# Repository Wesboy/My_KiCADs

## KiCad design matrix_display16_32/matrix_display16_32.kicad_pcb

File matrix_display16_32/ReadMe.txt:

更新
1 更换esp8266为esp32
3 更换TYPE-C座子
4 更换充电电池方案
5 电池电量检测
	电量低于20
6 充电提示ADC检测
7 天气
8 协议通信
   时间
   天气
   电量
   交互
   
下一版
 
9 增加两个贴片麦硅 AP3722AT

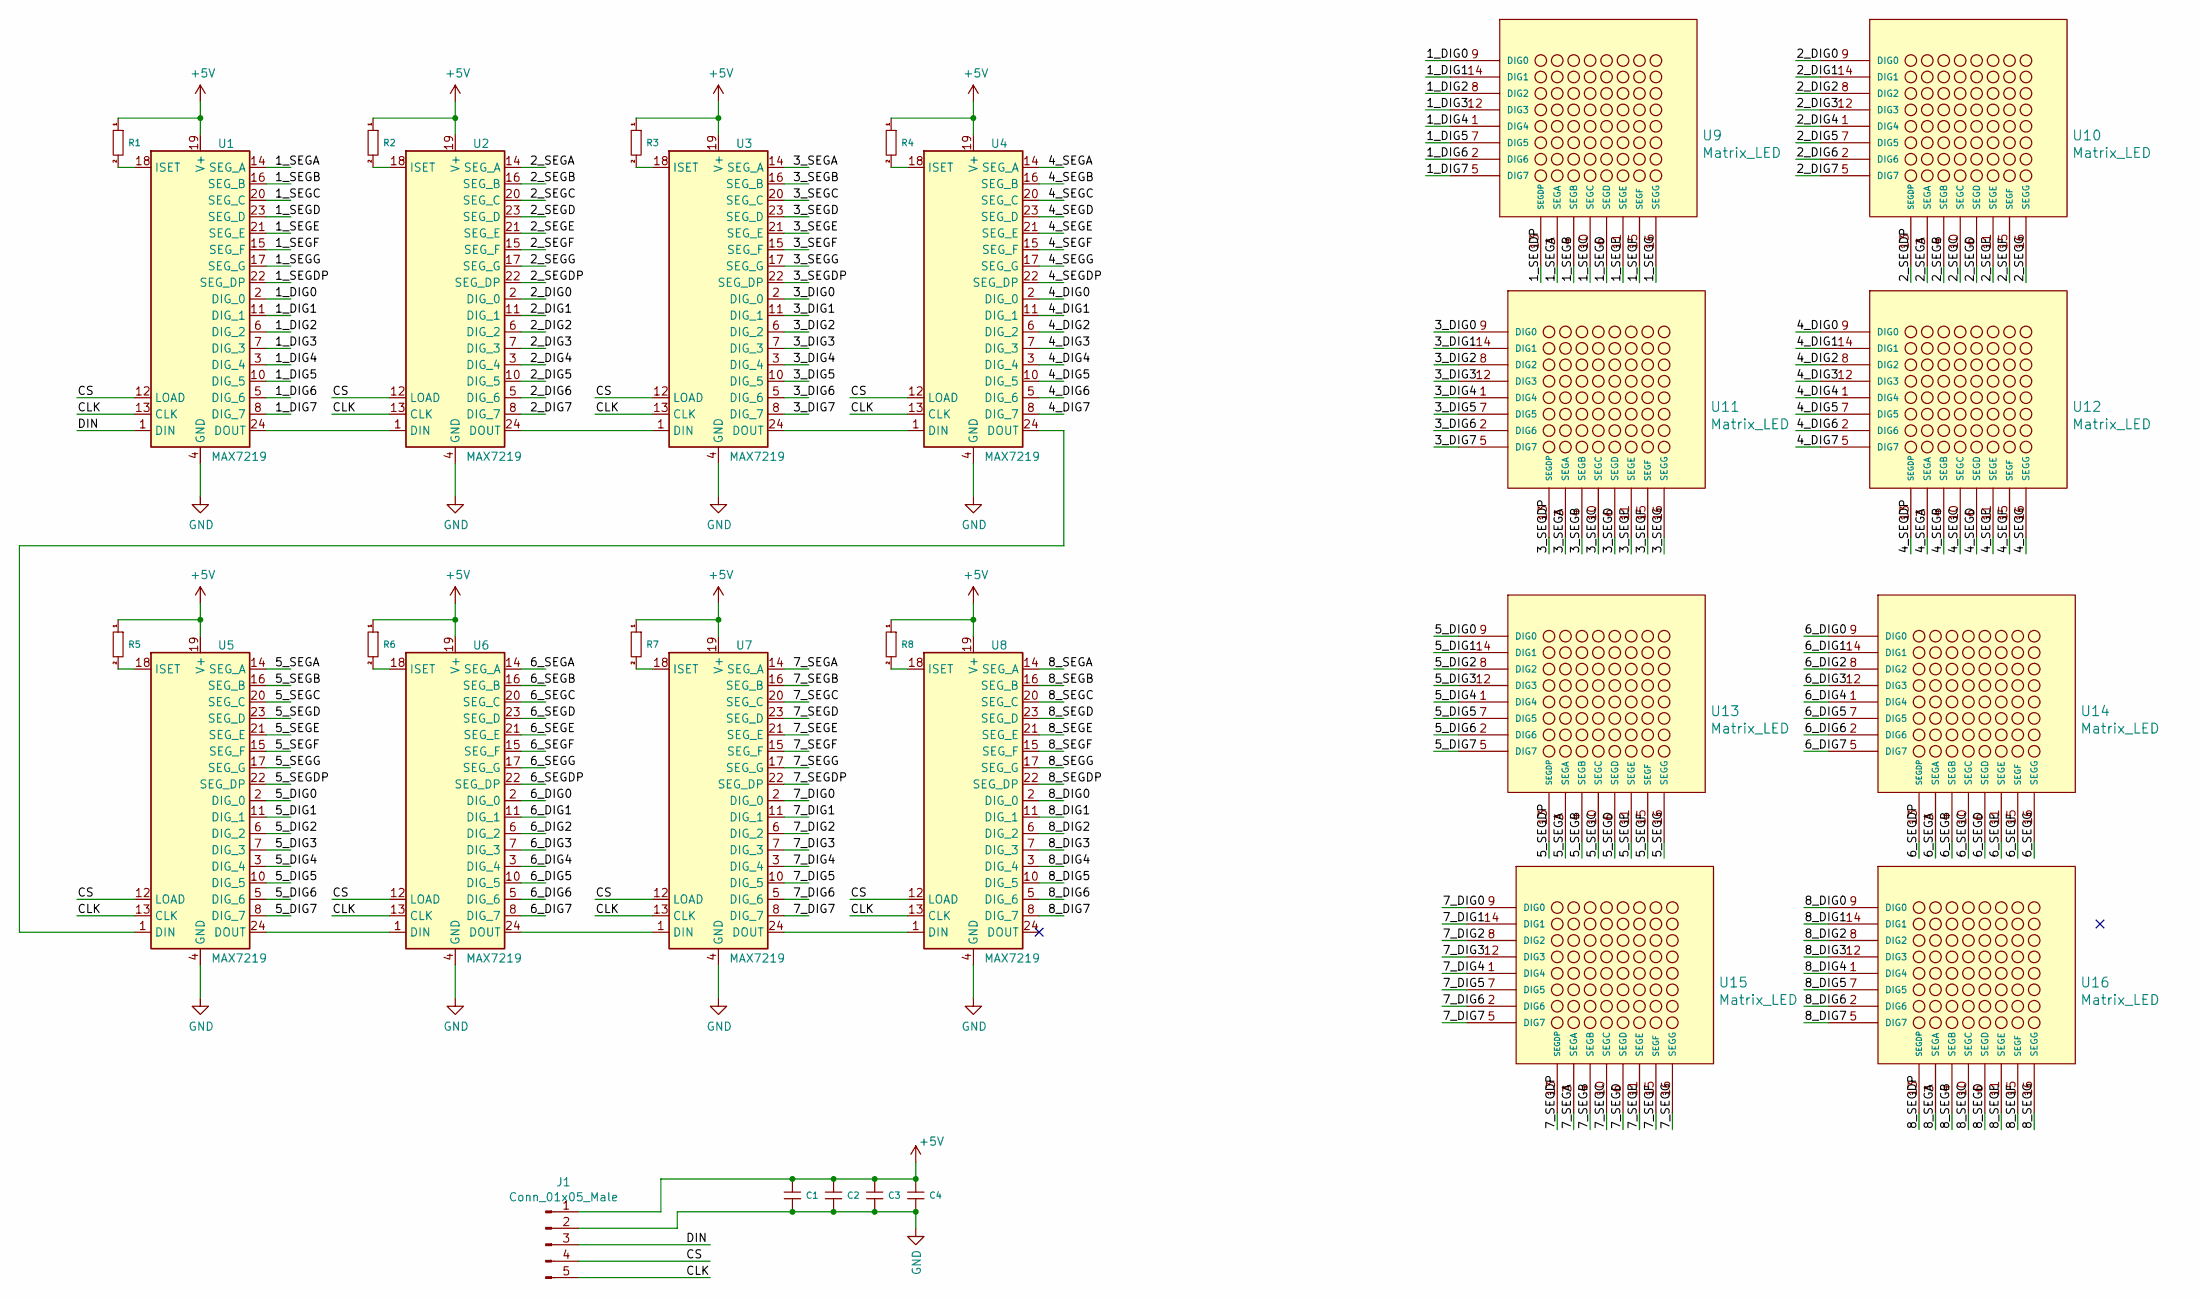
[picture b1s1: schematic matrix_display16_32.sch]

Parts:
C1, C2, C3, C4: C(MM)-LibCool; 0603_C
J1: Conn_01x05_Male; PinHeader_1x05_P2.54mm_Vertical
R1, R2, R3, R4, R5, R6, R7, R8: RES(M)-LibCool; 0603_R
U1, U2, U3, U4, U5, U6, U7, U8: MAX7219; SOIC-24W_7.5x15.4mm_P1.27mm
U9, U10, U11, U12, U13, U14, U15, U16: Matrix_LED

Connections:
+5V: C1.1, C2.1, C3.1, C4.1, J1.1, R1.1, R2.1, R3.1, R4.1, R5.1, R6.1, R7.1, R8.1, U1.19 (V+), U2.19 (V+), U3.19 (V+), U4.19 (V+), U5.19 (V+), U6.19 (V+), U7.19 (V+), U8.19 (V+)
/1_DIG0: U1.2 (DIG_0), U9.9 (DIG0)
/1_DIG1: U1.11 (DIG_1), U9.14 (DIG1)
/1_DIG2: U1.6 (DIG_2), U9.8 (DIG2)
/1_DIG3: U1.7 (DIG_3), U9.12 (DIG3)
/1_DIG4: U1.3 (DIG_4), U9.1 (DIG4)
/1_DIG5: U1.10 (DIG_5), U9.7 (DIG5)
/1_DIG6: U1.5 (DIG_6), U9.2 (DIG6)
/1_DIG7: U1.8 (DIG_7), U9.5 (DIG7)
/1_SEGA: U1.14 (SEG_A), U9.3 (SEGA)
/1_SEGB: U1.16 (SEG_B), U9.4 (SEGB)
/1_SEGC: U1.20 (SEG_C), U9.10 (SEGC)
/1_SEGD: U1.23 (SEG_D), U9.6 (SEGD)
/1_SEGDP: U1.22 (SEG_DP), U9.13 (SEGDP)
/1_SEGE: U1.21 (SEG_E), U9.11 (SEGE)
/1_SEGF: U1.15 (SEG_F), U9.15 (SEGF)
/1_SEGG: U1.17 (SEG_G), U9.16 (SEGG)
/2_DIG0: U2.2 (DIG_0), U10.9 (DIG0)
/2_DIG1: U2.11 (DIG_1), U10.14 (DIG1)
/2_DIG2: U2.6 (DIG_2), U10.8 (DIG2)
/2_DIG3: U2.7 (DIG_3), U10.12 (DIG3)
/2_DIG4: U2.3 (DIG_4), U10.1 (DIG4)
/2_DIG5: U2.10 (DIG_5), U10.7 (DIG5)
/2_DIG6: U2.5 (DIG_6), U10.2 (DIG6)
/2_DIG7: U2.8 (DIG_7), U10.5 (DIG7)
/2_SEGA: U2.14 (SEG_A), U10.3 (SEGA)
/2_SEGB: U2.16 (SEG_B), U10.4 (SEGB)
/2_SEGC: U2.20 (SEG_C), U10.10 (SEGC)
/2_SEGD: U2.23 (SEG_D), U10.6 (SEGD)
/2_SEGDP: U2.22 (SEG_DP), U10.13 (SEGDP)
/2_SEGE: U2.21 (SEG_E), U10.11 (SEGE)
/2_SEGF: U2.15 (SEG_F), U10.15 (SEGF)
/2_SEGG: U2.17 (SEG_G), U10.16 (SEGG)
/3_DIG0: U3.2 (DIG_0), U11.9 (DIG0)
/3_DIG1: U3.11 (DIG_1), U11.14 (DIG1)
/3_DIG2: U3.6 (DIG_2), U11.8 (DIG2)
/3_DIG3: U3.7 (DIG_3), U11.12 (DIG3)
/3_DIG4: U3.3 (DIG_4), U11.1 (DIG4)
/3_DIG5: U3.10 (DIG_5), U11.7 (DIG5)
/3_DIG6: U3.5 (DIG_6), U11.2 (DIG6)
/3_DIG7: U3.8 (DIG_7), U11.5 (DIG7)
/3_SEGA: U3.14 (SEG_A), U11.3 (SEGA)
/3_SEGB: U3.16 (SEG_B), U11.4 (SEGB)
/3_SEGC: U3.20 (SEG_C), U11.10 (SEGC)
/3_SEGD: U3.23 (SEG_D), U11.6 (SEGD)
/3_SEGDP: U3.22 (SEG_DP), U11.13 (SEGDP)
/3_SEGE: U3.21 (SEG_E), U11.11 (SEGE)
/3_SEGF: U3.15 (SEG_F), U11.15 (SEGF)
/3_SEGG: U3.17 (SEG_G), U11.16 (SEGG)
/4_DIG0: U4.2 (DIG_0), U12.9 (DIG0)
/4_DIG1: U4.11 (DIG_1), U12.14 (DIG1)
/4_DIG2: U4.6 (DIG_2), U12.8 (DIG2)
/4_DIG3: U4.7 (DIG_3), U12.12 (DIG3)
/4_DIG4: U4.3 (DIG_4), U12.1 (DIG4)
/4_DIG5: U4.10 (DIG_5), U12.7 (DIG5)
/4_DIG6: U4.5 (DIG_6), U12.2 (DIG6)
/4_DIG7: U4.8 (DIG_7), U12.5 (DIG7)
/4_SEGA: U4.14 (SEG_A), U12.3 (SEGA)
/4_SEGB: U4.16 (SEG_B), U12.4 (SEGB)
/4_SEGC: U4.20 (SEG_C), U12.10 (SEGC)
/4_SEGD: U4.23 (SEG_D), U12.6 (SEGD)
/4_SEGDP: U4.22 (SEG_DP), U12.13 (SEGDP)
/4_SEGE: U4.21 (SEG_E), U12.11 (SEGE)
/4_SEGF: U4.15 (SEG_F), U12.15 (SEGF)
/4_SEGG: U4.17 (SEG_G), U12.16 (SEGG)
/5_DIG0: U5.2 (DIG_0), U13.9 (DIG0)
/5_DIG1: U5.11 (DIG_1), U13.14 (DIG1)
/5_DIG2: U5.6 (DIG_2), U13.8 (DIG2)
/5_DIG3: U5.7 (DIG_3), U13.12 (DIG3)
/5_DIG4: U5.3 (DIG_4), U13.1 (DIG4)
/5_DIG5: U5.10 (DIG_5), U13.7 (DIG5)
/5_DIG6: U5.5 (DIG_6), U13.2 (DIG6)
/5_DIG7: U5.8 (DIG_7), U13.5 (DIG7)
/5_SEGA: U5.14 (SEG_A), U13.3 (SEGA)
/5_SEGB: U5.16 (SEG_B), U13.4 (SEGB)
/5_SEGC: U5.20 (SEG_C), U13.10 (SEGC)
/5_SEGD: U5.23 (SEG_D), U13.6 (SEGD)
/5_SEGDP: U5.22 (SEG_DP), U13.13 (SEGDP)
/5_SEGE: U5.21 (SEG_E), U13.11 (SEGE)
/5_SEGF: U5.15 (SEG_F), U13.15 (SEGF)
/5_SEGG: U5.17 (SEG_G), U13.16 (SEGG)
/6_DIG0: U6.2 (DIG_0), U14.9 (DIG0)
/6_DIG1: U6.11 (DIG_1), U14.14 (DIG1)
/6_DIG2: U6.6 (DIG_2), U14.8 (DIG2)
/6_DIG3: U6.7 (DIG_3), U14.12 (DIG3)
/6_DIG4: U6.3 (DIG_4), U14.1 (DIG4)
/6_DIG5: U6.10 (DIG_5), U14.7 (DIG5)
/6_DIG6: U6.5 (DIG_6), U14.2 (DIG6)
/6_DIG7: U6.8 (DIG_7), U14.5 (DIG7)
/6_SEGA: U6.14 (SEG_A), U14.3 (SEGA)
/6_SEGB: U6.16 (SEG_B), U14.4 (SEGB)
/6_SEGC: U6.20 (SEG_C), U14.10 (SEGC)
/6_SEGD: U6.23 (SEG_D), U14.6 (SEGD)
/6_SEGDP: U6.22 (SEG_DP), U14.13 (SEGDP)
/6_SEGE: U6.21 (SEG_E), U14.11 (SEGE)
/6_SEGF: U6.15 (SEG_F), U14.15 (SEGF)
/6_SEGG: U6.17 (SEG_G), U14.16 (SEGG)
/7_DIG0: U7.2 (DIG_0), U15.9 (DIG0)
/7_DIG1: U7.11 (DIG_1), U15.14 (DIG1)
/7_DIG2: U7.6 (DIG_2), U15.8 (DIG2)
/7_DIG3: U7.7 (DIG_3), U15.12 (DIG3)
/7_DIG4: U7.3 (DIG_4), U15.1 (DIG4)
/7_DIG5: U7.10 (DIG_5), U15.7 (DIG5)
/7_DIG6: U7.5 (DIG_6), U15.2 (DIG6)
/7_DIG7: U7.8 (DIG_7), U15.5 (DIG7)
/7_SEGA: U7.14 (SEG_A), U15.3 (SEGA)
/7_SEGB: U7.16 (SEG_B), U15.4 (SEGB)
/7_SEGC: U7.20 (SEG_C), U15.10 (SEGC)
/7_SEGD: U7.23 (SEG_D), U15.6 (SEGD)
/7_SEGDP: U7.22 (SEG_DP), U15.13 (SEGDP)
/7_SEGE: U7.21 (SEG_E), U15.11 (SEGE)
/7_SEGF: U7.15 (SEG_F), U15.15 (SEGF)
/7_SEGG: U7.17 (SEG_G), U15.16 (SEGG)
/8_DIG0: U8.2 (DIG_0), U16.9 (DIG0)
/8_DIG1: U8.11 (DIG_1), U16.14 (DIG1)
/8_DIG2: U8.6 (DIG_2), U16.8 (DIG2)
/8_DIG3: U8.7 (DIG_3), U16.12 (DIG3)
/8_DIG4: U8.3 (DIG_4), U16.1 (DIG4)
/8_DIG5: U8.10 (DIG_5), U16.7 (DIG5)
/8_DIG6: U8.5 (DIG_6), U16.2 (DIG6)
/8_DIG7: U8.8 (DIG_7), U16.5 (DIG7)
/8_SEGA: U8.14 (SEG_A), U16.3 (SEGA)
/8_SEGB: U8.16 (SEG_B), U16.4 (SEGB)
/8_SEGC: U8.20 (SEG_C), U16.10 (SEGC)
/8_SEGD: U8.23 (SEG_D), U16.6 (SEGD)
/8_SEGDP: U8.22 (SEG_DP), U16.13 (SEGDP)
/8_SEGE: U8.21 (SEG_E), U16.11 (SEGE)
/8_SEGF: U8.15 (SEG_F), U16.15 (SEGF)
/8_SEGG: U8.17 (SEG_G), U16.16 (SEGG)
/CLK: J1.5, U1.13 (CLK), U2.13 (CLK), U3.13 (CLK), U4.13 (CLK), U5.13 (CLK), U6.13 (CLK), U7.13 (CLK), U8.13 (CLK)
/CS: J1.4, U1.12 (LOAD), U2.12 (LOAD), U3.12 (LOAD), U4.12 (LOAD), U5.12 (LOAD), U6.12 (LOAD), U7.12 (LOAD), U8.12 (LOAD)
/DIN: J1.3, U1.1 (DIN)
GND: C1.2, C2.2, C3.2, C4.2, J1.2, U1.4 (GND), U1.9 (GND), U2.4 (GND), U2.9 (GND), U3.4 (GND), U3.9 (GND), U4.4 (GND), U4.9 (GND), U5.4 (GND), U5.9 (GND), U6.4 (GND), U6.9 (GND), U7.4 (GND), U7.9 (GND), U8.4 (GND), U8.9 (GND)
unnamed: R1.2, U1.18 (ISET)
unnamed: R2.2, U2.18 (ISET)
unnamed: R3.2, U3.18 (ISET)
unnamed: R4.2, U4.18 (ISET)
unnamed: R5.2, U5.18 (ISET)
unnamed: R6.2, U6.18 (ISET)
unnamed: R7.2, U7.18 (ISET)
unnamed: R8.2, U8.18 (ISET)
unnamed: U1.24 (DOUT), U2.1 (DIN)
unnamed: U2.24 (DOUT), U3.1 (DIN)
unnamed: U3.24 (DOUT), U4.1 (DIN)
unnamed: U4.24 (DOUT), U5.1 (DIN)
unnamed: U5.24 (DOUT), U6.1 (DIN)
unnamed: U6.24 (DOUT), U7.1 (DIN)
unnamed: U7.24 (DOUT), U8.1 (DIN)

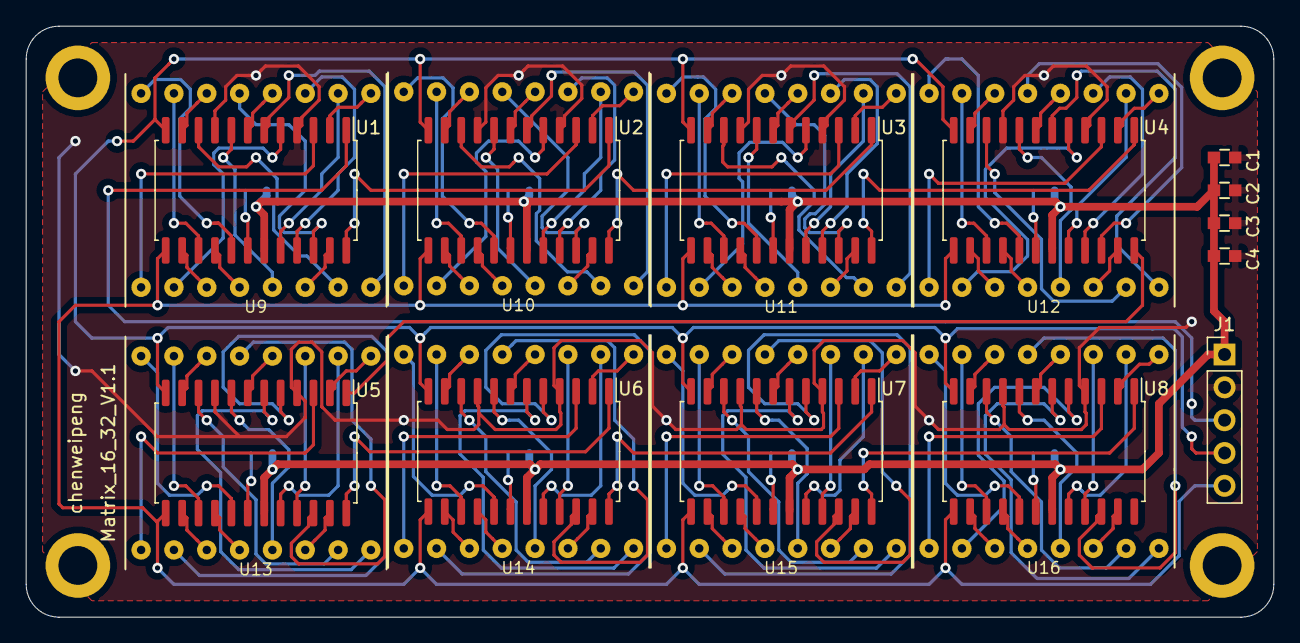
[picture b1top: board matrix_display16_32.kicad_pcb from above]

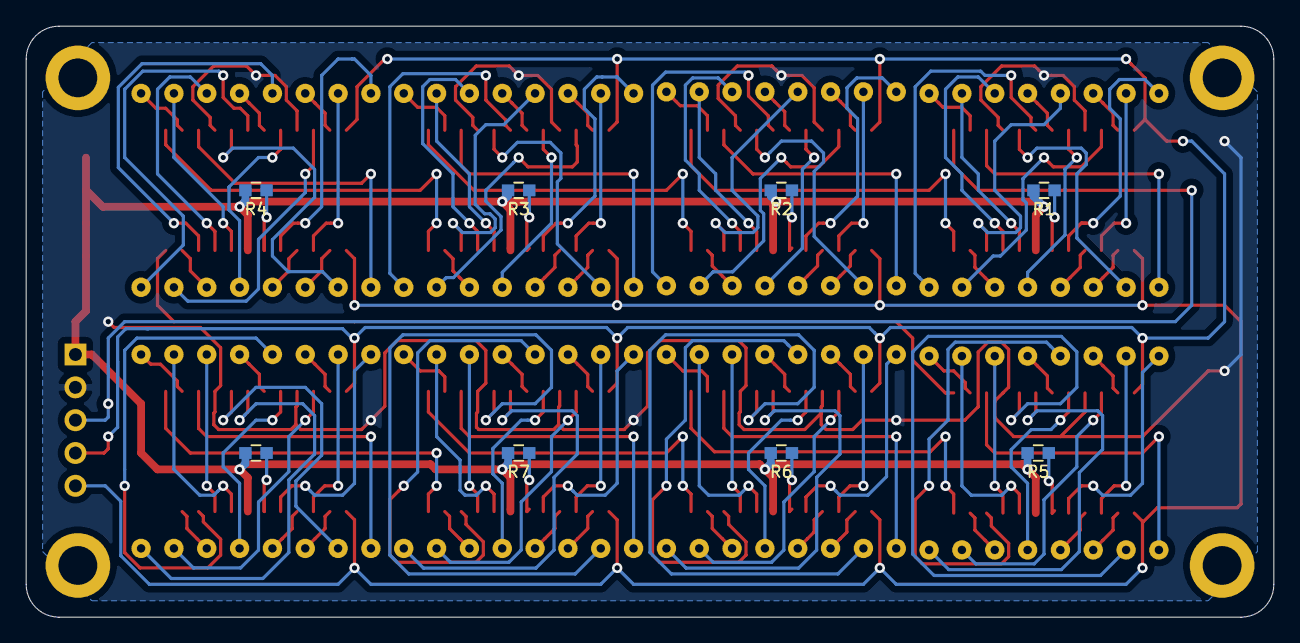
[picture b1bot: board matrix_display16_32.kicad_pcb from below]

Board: 2 copper layers, 96.5 x 45.7 mm, 29 parts (8 on the bottom side), 148 nets.

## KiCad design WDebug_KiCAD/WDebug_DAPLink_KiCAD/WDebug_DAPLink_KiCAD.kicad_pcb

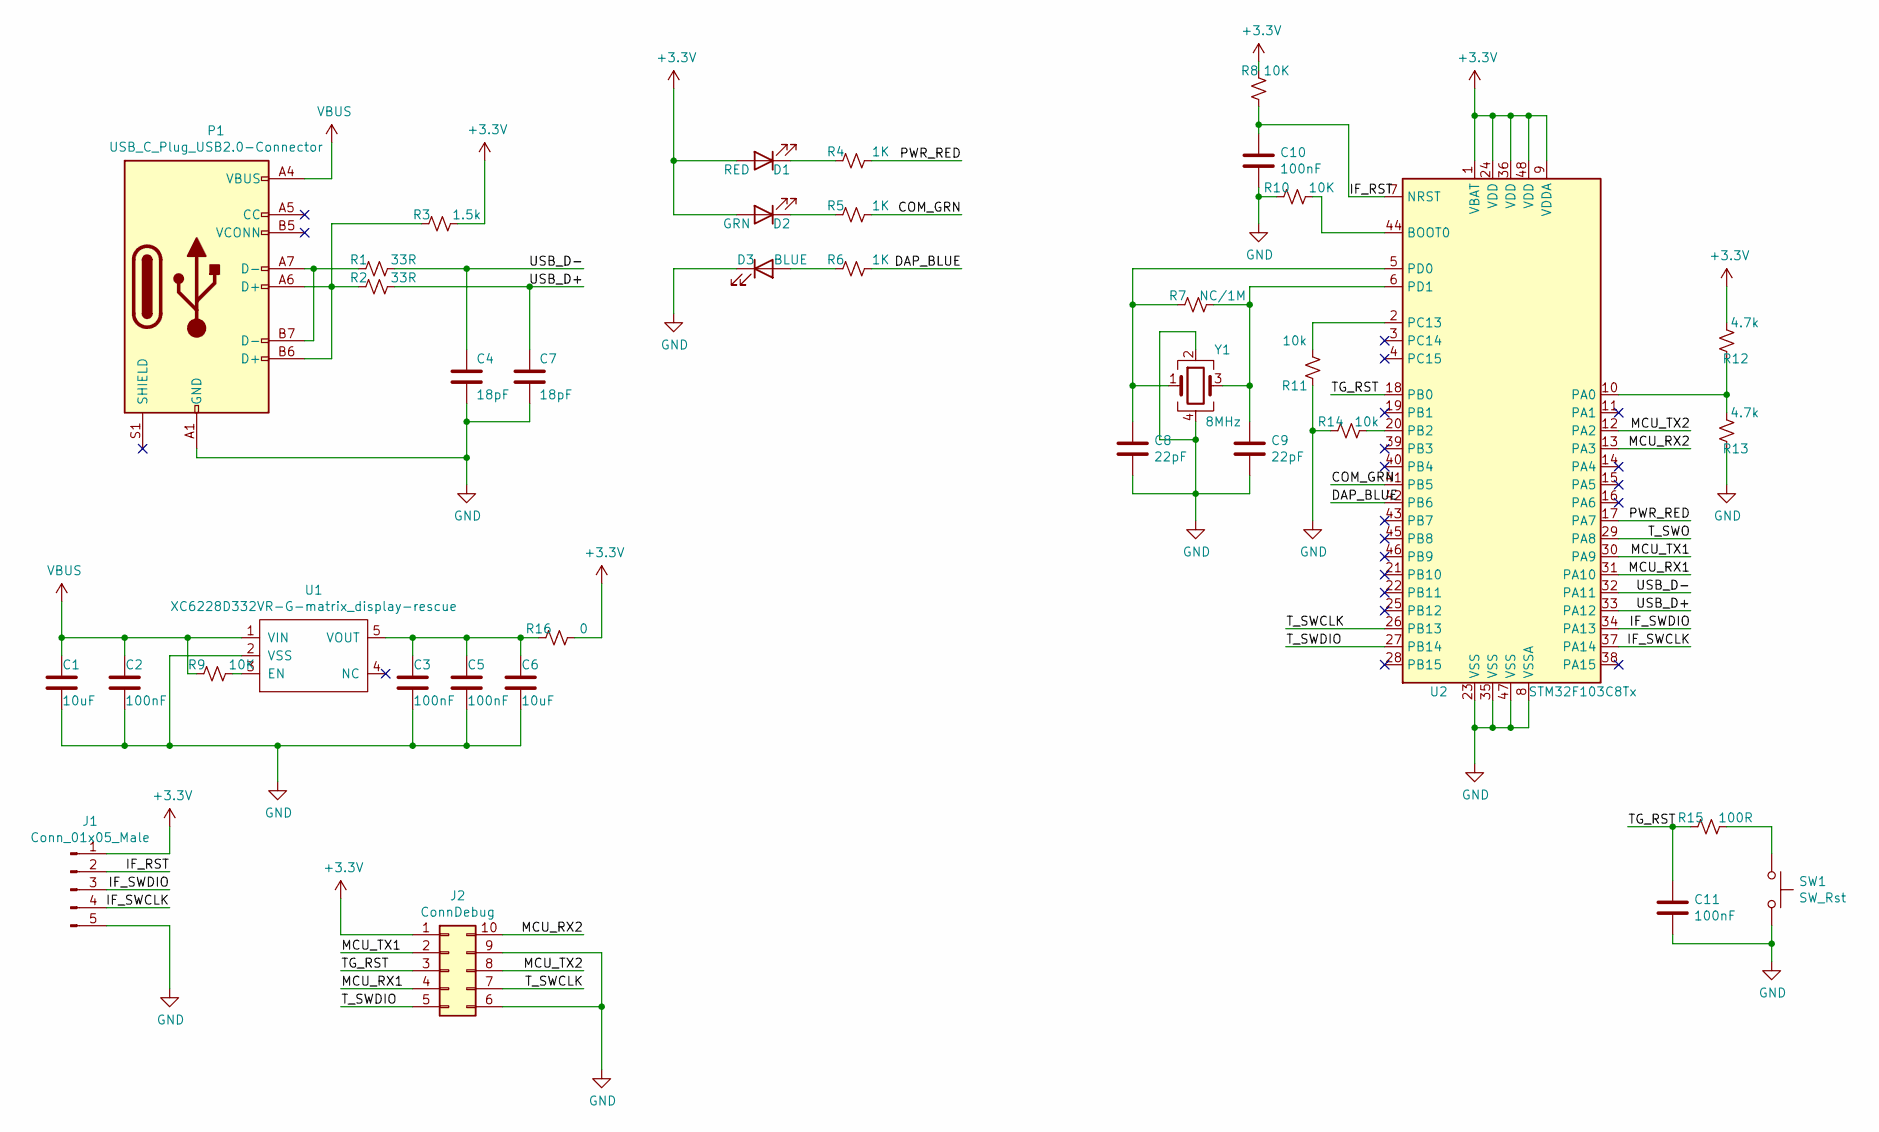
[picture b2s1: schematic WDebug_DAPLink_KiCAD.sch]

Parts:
C1, C6: 10uF; C_0805_2012Metric
C2, C3, C5, C10, C11: 100nF; C_0603_1608Metric
C4, C7: 18pF; C_0603_1608Metric
C8, C9: 22pF; C_0603_1608Metric
D1: RED; LED_0603_1608Metric
D2: GRN; LED_0603_1608Metric
D3: BLUE; LED_0603_1608Metric
J1: Conn_01x05_Male; PinHeader_1x05_P2.54mm_Vertical
J2: ConnDebug; PinHeader_2x05_P2.54mm_Vertical
P1: USB_C_Plug_USB2.0-Connector; USB-C-SMD_KH-TYPE-C-16P
R1, R2: 33R; R_0603_1608Metric
R3: 1.5k; R_0603_1608Metric
R4, R5, R6: 1K; R_0603_1608Metric
R7: NC/1M; R_0603_1608Metric
R8, R9, R10: 10K; R_0603_1608Metric
R11, R14: 10k; R_0603_1608Metric
R12, R13: 4.7k; R_0603_1608Metric
R15: 100R; R_0603_1608Metric
R16: 0; R_0603_1608Metric
SW1: SW_Rst; SWITCH_PUSH
U1: XC6228D332VR-G-matrix_display-rescue; SOT23-5
U2: STM32F103C8Tx; LQFP-48_7x7mm_P0.5mm
Y1: 8MHz; Crystal_SMD_3225-4Pin_3.2x2.5mm

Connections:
+3V3: D1.2 (A), D2.2 (A), J1.1, J2.1, R3.1, R8.1, R12.1, R16.1, U2.1 (VBAT), U2.9 (VDDA), U2.24 (VDD), U2.36 (VDD), U2.48 (VDD)
/COM_GRN: R5.1, U2.41 (PB5)
/DAP_BLUE: R6.1, U2.42 (PB6)
/IF_RST: C10.1, J1.2, R8.2, U2.7 (NRST)
/IF_SWCLK: J1.4, U2.37 (PA14)
/IF_SWDIO: J1.3, U2.34 (PA13)
/MCU_RX1: J2.4, U2.31 (PA10)
/MCU_RX2: J2.10, U2.13 (PA3)
/MCU_TX1: J2.2, U2.30 (PA9)
/MCU_TX2: J2.8, U2.12 (PA2)
/PWR_RED: R4.1, U2.17 (PA7)
/TG_RST: C11.1, J2.3, R15.2, U2.18 (PB0)
/T_SWCLK: J2.7, U2.26 (PB13)
/T_SWDIO: J2.5, U2.27 (PB14)
/T_SWO: U2.29 (PA8)
/USB_D+: C7.1, R2.1, U2.33 (PA12)
/USB_D-: C4.1, R1.1, U2.32 (PA11)
GND: C1.2, C2.2, C3.2, C4.2, C5.2, C6.2, C7.2, C8.2, C9.2, C10.2, C11.2, D3.1 (K), J1.5, J2.6, J2.9, P1.A1 (GND), P1.A12 (GND), P1.B1 (GND), P1.B12 (GND), R10.2, R11.2, R13.2, R14.1, SW1.2, U1.2 (VSS), U2.8 (VSSA), U2.23 (VSS), U2.35 (VSS), U2.47 (VSS), Y1.2, Y1.4
unnamed: C3.1, C5.1, C6.1, R16.2, U1.5 (VOUT)
unnamed: C8.1, R7.2, U2.5 (PD0), Y1.1
unnamed: C9.1, R7.1, U2.6 (PD1), Y1.3
unnamed: D1.1 (K), R4.2
unnamed: D2.1 (K), R5.2
unnamed: D3.2 (A), R6.2
unnamed: P1.A6 (D+), P1.B6 (D+), R2.2, R3.2
unnamed: P1.A7 (D-), P1.B7 (D-), R1.2
unnamed: R9.1, U1.3 (EN)
unnamed: R10.1, U2.44 (BOOT0)
unnamed: R11.1, U2.2 (PC13)
unnamed: R12.2, R13.1, U2.10 (PA0)
unnamed: R14.2, U2.20 (PB2)
unnamed: R15.1, SW1.1
VBUS: C1.1, C2.1, P1.A4 (VBUS), P1.A9 (VBUS), P1.B4 (VBUS), P1.B9 (VBUS), R9.2, U1.1 (VIN)

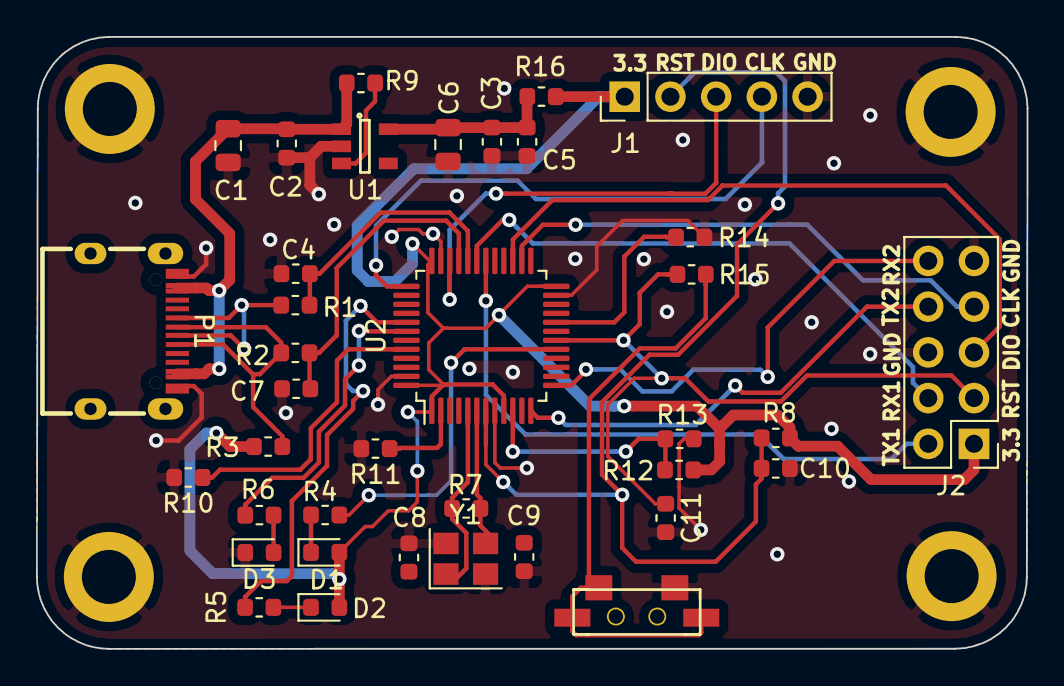
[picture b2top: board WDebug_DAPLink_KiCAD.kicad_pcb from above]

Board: 2 copper layers, 55.0 x 34.0 mm, 37 parts (0 on the bottom side), 32 nets.

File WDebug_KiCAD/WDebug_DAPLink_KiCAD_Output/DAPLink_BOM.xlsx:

Reference | Value | Footprint | Datasheet
U2 | STM32F103C8Tx | Package_QFP:LQFP-48_7x7mm_P0.5mm
J1 | Conn_01x04 | Connector_PinHeader_2.54mm:PinHeader_1x04_P2.54mm_Vertical | ~
D3 | BLUE | LED_SMD:LED_0603_1608Metric | ~
D1 | RED | LED_SMD:LED_0603_1608Metric | ~
D2 | GRN | LED_SMD:LED_0603_1608Metric | ~
C10 | 100nF | Capacitor_SMD:C_0603_1608Metric | ~
C4 | 18pF | Capacitor_SMD:C_0603_1608Metric | ~
C7 | 18pF | Capacitor_SMD:C_0603_1608Metric | ~
C9 | 22pF | Capacitor_SMD:C_0603_1608Metric | ~
C8 | 22pF | Capacitor_SMD:C_0603_1608Metric | ~
Y1 | 8MHz | Crystal:Crystal_SMD_5032-4Pin_5.0x3.2mm | ~
R7 | NC/1M | Resistor_SMD:R_0603_1608Metric | ~
R10 | 10K | Resistor_SMD:R_0603_1608Metric | ~
R8 | 10K | Resistor_SMD:R_0603_1608Metric | ~
R6 | 1K | Resistor_SMD:R_0603_1608Metric | ~
R5 | 1K | Resistor_SMD:R_0603_1608Metric | ~
R4 | 1K | Resistor_SMD:R_0603_1608Metric | ~
R13 | 4.7k | Resistor_SMD:R_0603_1608Metric | ~
R12 | 4.7k | Resistor_SMD:R_0603_1608Metric | ~
R3 | 1.5k | Resistor_SMD:R_0603_1608Metric | ~
R2 | 33R | Resistor_SMD:R_0603_1608Metric | ~
R1 | 33R | Resistor_SMD:R_0603_1608Metric | ~
P1 | USB_C_Plug_USB2.0 | WDebug_DAPLink:USB-Type-C | https://www.usb.org/sites/default/files/documents/usb_type-c.zip
R11 | 10k | Resistor_SMD:R_0603_1608Metric | ~
R14 | 10k | Resistor_SMD:R_0603_1608Metric | ~
J5 | 01x18_Female_Fan | WDebug_DAPLink:1x16_P1.0mm | ~
J2 | Conn_02x04_UART_SW | Connector_PinHeader_2.54mm:PinHeader_2x04_P2.54mm_Vertical | ~
SW1 | SW_Rst | WDebug_DAPLink:SWITCH_PUSH | ~
R15 | 100R | Resistor_SMD:R_0603_1608Metric | ~
C11 | 100nF | Capacitor_SMD:C_0603_1608Metric | ~
J3 | Conn_01x20_Female | WDebug_KiCAD:1x18_P1.0mm | ~
J4 | Conn_01x05_Male | Connector_PinHeader_2.54mm:PinHeader_1x05_P2.54mm_Vertical | ~
U1 | XC6228D332VR-G-matrix_display-rescue | matrix_control_main:SOT23-5
C1 | 10uF | Capacitor_SMD:C_0603_1608Metric | ~
C3 | 100nF | Capacitor_SMD:C_0603_1608Metric | ~
C5 | 100nF | Capacitor_SMD:C_0603_1608Metric | ~
C6 | 10uF | Capacitor_SMD:C_0603_1608Metric | ~
C2 | 100nF | Capacitor_SMD:C_0603_1608Metric | ~
R9 | 10K | Resistor_SMD:R_0603_1608Metric | ~
J6 | 3.3V_Conn | Connector_PinHeader_2.54mm:PinHeader_1x02_P2.54mm_Vertical | ~

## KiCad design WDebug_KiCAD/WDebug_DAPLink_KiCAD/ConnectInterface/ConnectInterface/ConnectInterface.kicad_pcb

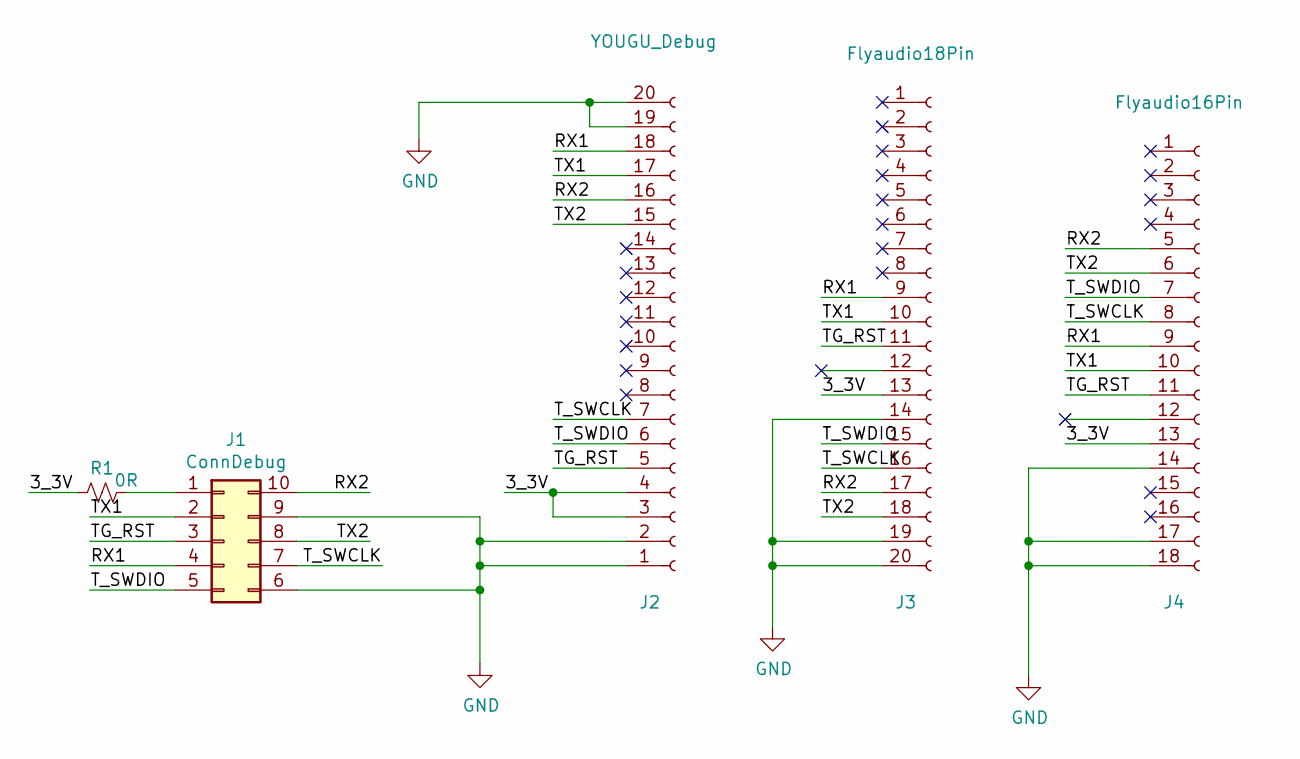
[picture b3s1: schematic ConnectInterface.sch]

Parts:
J1: ConnDebug; PinHeader_2x05_P2.54mm_Vertical
J2: YOUGU_Debug; 1x18_P1.0mm
J3: Flyaudio18Pin; 1x18_P1.0mm
J4: Flyaudio16Pin; 1x16_P1.0mm
R1: 0R; R_0603_1608Metric

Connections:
/3_3V: J2.3, J2.4, J3.13, J4.13, R1.1
/RX1: J1.4, J2.18, J3.9, J4.9
/RX2: J1.10, J2.16, J3.17, J4.5
/TG_RST: J1.3, J2.5, J3.11, J4.11
/TX1: J1.2, J2.17, J3.10, J4.10
/TX2: J1.8, J2.15, J3.18, J4.6
/T_SWCLK: J1.7, J2.7, J3.16, J4.8
/T_SWDIO: J1.5, J2.6, J3.15, J4.7
GND: J1.6, J1.9, J2.1, J2.2, J2.19, J2.20, J3.14, J3.19, J3.20, J4.14, J4.17, J4.18
unnamed: J1.1, R1.2

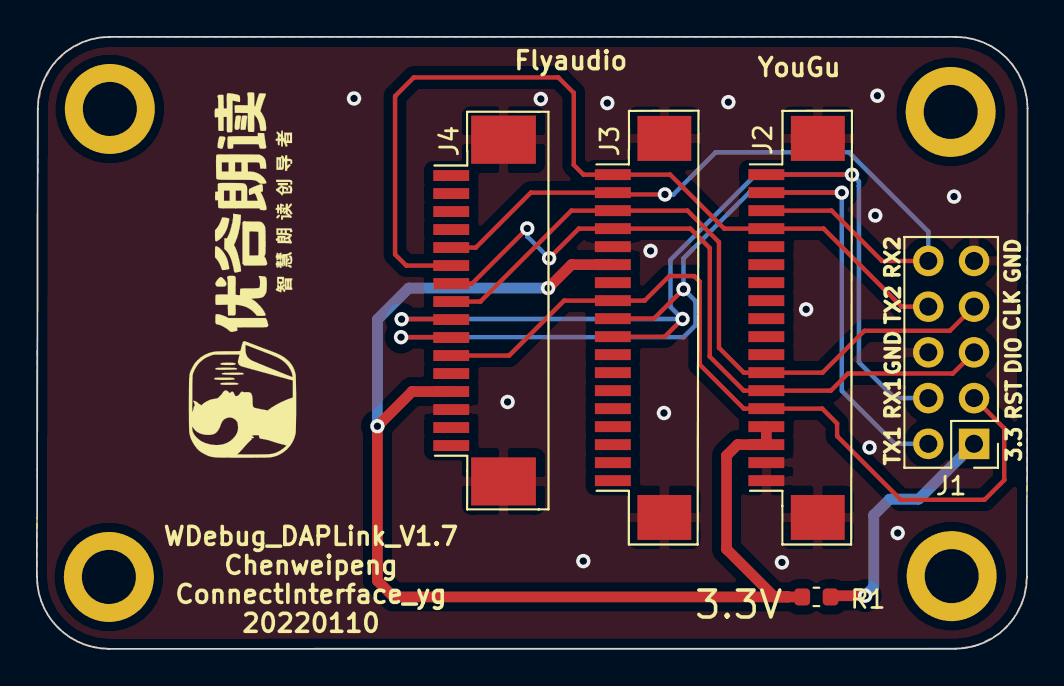
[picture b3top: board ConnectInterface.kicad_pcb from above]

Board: 2 copper layers, 55.0 x 34.0 mm, 9 parts (0 on the bottom side), 10 nets.

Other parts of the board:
1, 2, 3, 4: hanpan

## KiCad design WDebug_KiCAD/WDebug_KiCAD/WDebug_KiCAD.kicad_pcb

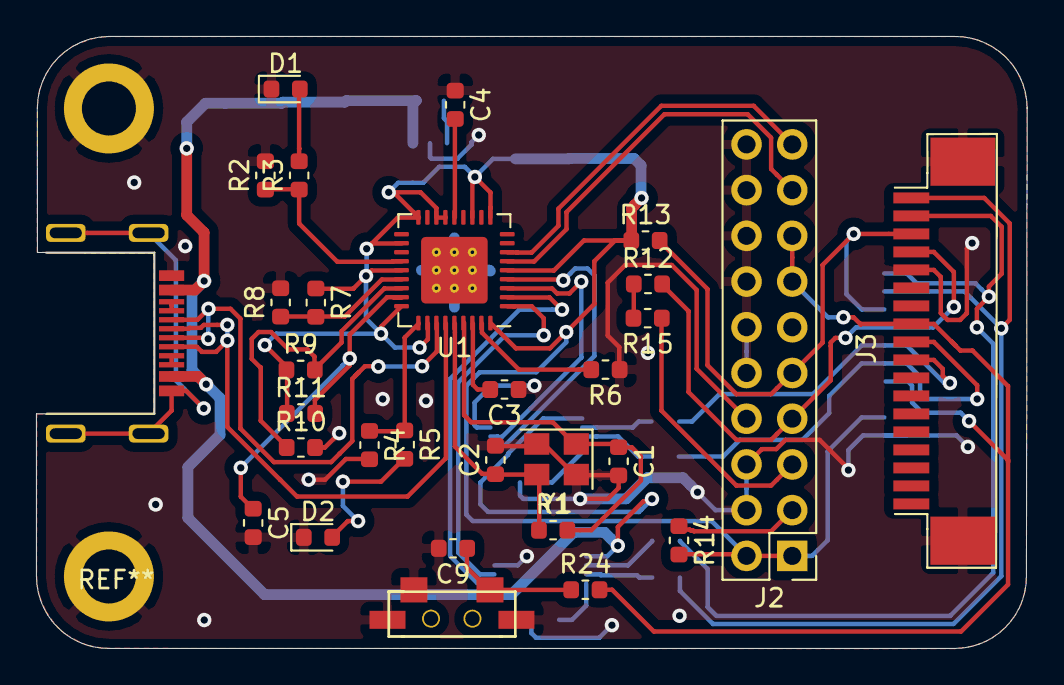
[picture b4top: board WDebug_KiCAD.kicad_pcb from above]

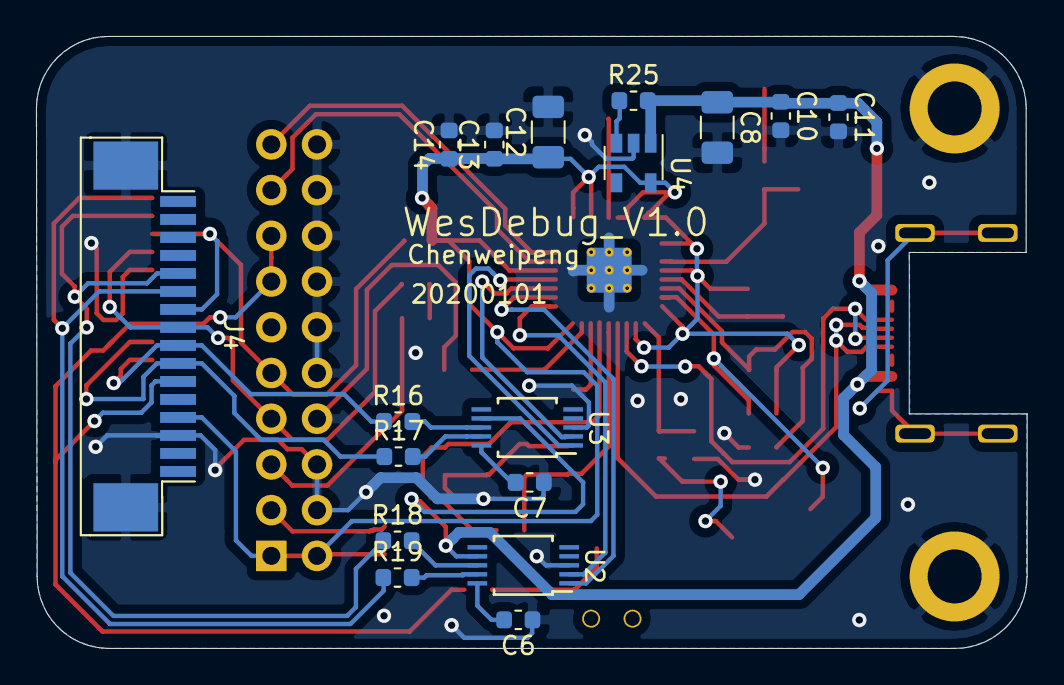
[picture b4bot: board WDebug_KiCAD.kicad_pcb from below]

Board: 2 copper layers, 55.0 x 34.0 mm, 47 parts (17 on the bottom side), 41 nets.

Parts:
C1, C2: 22pF; C_0603_1608Metric
C3, C4, C9, C10, C13, C14: 100nF; C_0603_1608Metric
C5: 1uF; C_0603_1608Metric
C6, C7: 0.1uF; C_0603_1608Metric
C8, C12: 10uF; C_1206_3216Metric
C11: 220pF; C_0603_1608Metric
D1: GRN; LED_0603_1608Metric
D2: RED; LED_0603_1608Metric
J1: USB_C_Receptacle_USB2.0; USB-Type-C
J2: HD2*10; PinHeader_2x10_P2.54mm_Vertical
J3: 20p; 1x18_P1.0mm
J4: 18p; 1x16_P1.0mm
R1: 1M; R_0603_1608Metric
R2, R4: 1K; R_0603_1608Metric
R3, R5: 100R; R_0603_1608Metric
R6: 12k; R_0603_1608Metric
R7, R10: NC; R_0603_1608Metric
R8, R9, R11, R12, R13, R14, R15, R25: 10K; R_0603_1608Metric
R16, R18: 820R; R_0603_1608Metric
R17, R19: 22R; R_0603_1608Metric
R24: 110R; R_0603_1608Metric
SW1: sw; SWITCH_PUSH
U1: USB2514B_Bi; QFN-36-1EP_6x6mm_P0.5mm_EP3.7x3.7mm_ThermalVias
U2, U3: CH340E; TSSOP-10_3x3mm_P0.5mm
U4: SPX3819M5-L; SOT-23-5
Y1: 24MHz; Crystal_SMD_Abracon_ABM8G-4Pin_3.2x2.5mm

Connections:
+3V3: C12.1, C13.1, C14.1, J2.1, J2.2, J4.13, R7.1, R9.1, R11.1, R13.1, R14.2, U1.5, U1.10, U1.12, U1.15, U1.16, U1.18, U1.20, U1.23, U1.27, U1.29, U1.36, U4.5
+5V: C8.1, C10.1, C11.1, J1.A4, R25.2, U2.7, U3.7, U4.1
/CLK_IN: C1.1, R1.2, U1.33, Y1.1
/CLK_OUT: C2.1, R1.1, U1.32, Y1.3
/JTCK: J2.9, J3.16, J4.7, R13.2
/JTDI: J2.5, R15.1
/JTMS: J2.7, J3.15, J4.8, R12.2
/JTRST: J2.3, R14.1
/KEY_RST: J2.13, J2.15, J3.11, J4.11, R24.2
/REM0: R4.1, R5.1, U1.28
/REM1: R2.1, R3.1, U1.22
/RST: C5.1, R11.2, U1.26
/RX1: J3.18, J4.6, R19.1
/RX2: J3.10, J4.10, R17.1
/SEL0: R7.2, R8.1, U1.24
/SEL1: R9.2, R10.1, U1.25
/TX1: J3.17, J4.5, R18.1
/TX2: J3.9, J4.9, R16.1
/USB1+: U1.2, U2.1
/USB1-: U1.1, U2.2
/USB2+: U1.4, U3.1
/USB2-: U1.3, U3.2
/USB3+: J2.19, U1.7
/USB3-: J2.17, U1.6
GND: C1.2, C2.2, C3.1, C4.1, C5.2, C6.1, C7.1, C8.2, C9.2, C10.2, C11.2, C12.2, C13.2, C14.2, D1.1, D2.1, J1.A1, J2.4, J2.6, J2.8, J2.10, J2.12, J2.14, J2.16, J2.18, J2.20, J3.14, J3.19, J3.20, J4.14, J4.17, J4.18, R2.2, R4.2, R6.1, R8.2, R10.2, SW1.1, U1.37, U2.3, U3.3, U4.2, Y1.2, Y1.4
unnamed: C3.2, U1.34
unnamed: C4.2, U1.14
unnamed: C6.2, U2.10
unnamed: C7.2, U3.10
unnamed: C9.1, R24.1, SW1.2
unnamed: D1.2, R3.2
unnamed: D2.2, R5.2
unnamed: J1.A6, U1.31
unnamed: J1.A7, U1.30
unnamed: R6.2, U1.35
unnamed: R12.1, R15.2
unnamed: R16.2, U3.8
unnamed: R17.2, U3.9
unnamed: R18.2, U2.8
unnamed: R19.2, U2.9
unnamed: R25.1, U4.3

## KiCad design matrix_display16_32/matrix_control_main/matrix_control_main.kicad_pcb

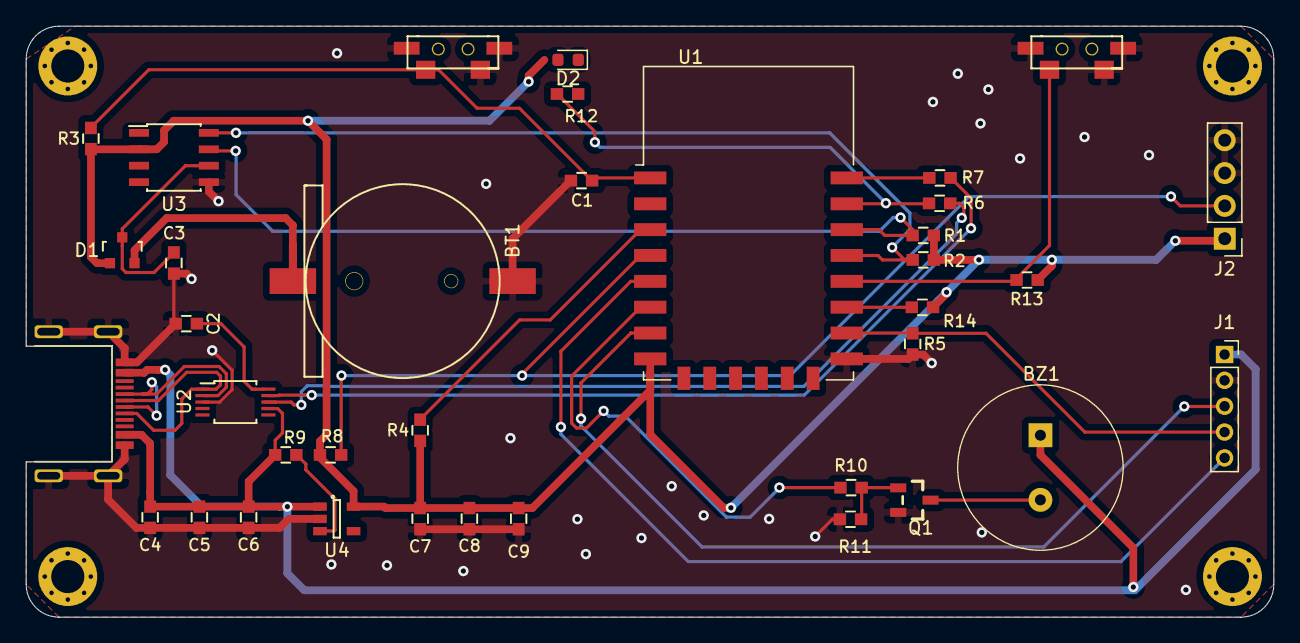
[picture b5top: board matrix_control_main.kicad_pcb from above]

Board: 2 copper layers, 96.5 x 45.7 mm, 37 parts (0 on the bottom side), 26 nets.

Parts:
BT1: BATTERY; CR1220-SMD
BZ1: PS1240P02BT; Piezo_Transducer_THT_PS1240P02BT
C1: 0.1uf; 0603_C
C2: 01.uF; 0603_C
C3: 0.1uF; 0603_C
C4: 10UF; 0603_C
C5: 100NF; 0603_C
C6: 220PF; 0603_C
C7, C8, C9: 10uf; 0603_C
D1: BAT54C; SOT-23
D2: 0603_绿灯; LED_0603_1608Metric
J1: Conn_01x05_Male; PinSocket_1x05_P2.00mm_Vertical
J2: Conn_01x04_Male; Pin_1x04_P2.54mm_DHT11
P1: Connector_USB_C_Plug_USB2.0; USB-Type-C
Q1: SOT-23_SS8050_Y1; SOT-23(SOT-23-3)
R1, R2, R3, R4, R5, R9, R10, R11, R13, R14: 10K; 0603_R
R6, R7: 100R; 0603_R
R8: 4.7k; 0603_R
R12: 1K; 0603_R
SW1: RST; SWITCH_PUSH
SW2: Dowload; SWITCH_PUSH
U1: ESP-12; ESP-12E
U2: CH340E; TSSOP-10_3x3mm_P0.5mm
U3: DS3231; SOP-8
U4: XC6228D332VR-G; SOT23-5

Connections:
+3V3: C7.1, C8.1, C9.1, D1.1, J2.1, R1.1, R2.1, R3.1, R4.1, R8.1, R13.1, R14.1, U1.8, U3.2, U4.5
+5V: BZ1.1, C4.1, C5.1, C6.2, J1.1, P1.A4, R9.1, U2.7, U4.1
/BEEP_IN: R10.1, U1.6
/CLK: J1.5, U1.5
/CS: J1.4, R5.1, U1.16
/DIN: J1.3, U1.7
/RXD: R7.2, U1.22
/SCL: R2.2, U1.19, U3.8
/SDA: R1.2, U1.20, U3.7
/TXD: R6.2, R12.2, U1.21
/T_DAT: J2.2, R8.2, U1.4
GND: BT1.2, C1.2, C2.2, C3.1, C4.2, C5.2, C6.1, C7.2, C8.2, C9.2, J1.2, J2.3, J2.4, P1.A1, P1.S1, Q1.2, R5.2, R11.2, SW1.1, SW2.1, U1.15, U2.3, U3.5, U4.2
unnamed: BT1.1, D1.2
unnamed: BZ1.2, Q1.3
unnamed: C1.1, R3.2, SW1.2, U1.1
unnamed: C2.1, U2.10
unnamed: C3.2, D1.3, U3.6
unnamed: P1.A6, U2.1
unnamed: P1.A7, U2.2
unnamed: Q1.1, R10.2, R11.1
unnamed: R4.2, U1.3
unnamed: R6.1, U2.8
unnamed: R7.1, U2.9
unnamed: R9.2, U4.3
unnamed: R13.2, SW2.2, U1.18
unnamed: R14.2, U1.17

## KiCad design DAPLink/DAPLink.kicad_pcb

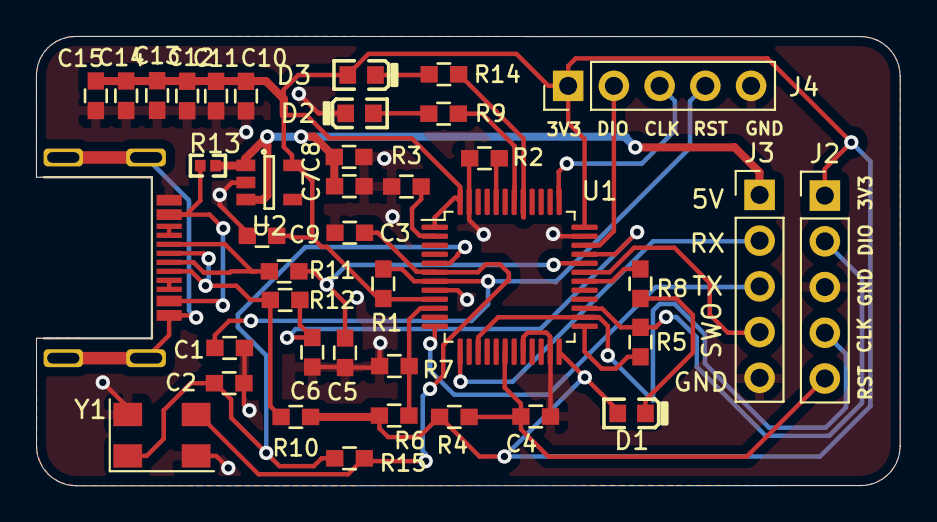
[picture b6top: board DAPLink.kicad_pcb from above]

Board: 2 copper layers, 48.0 x 25.0 mm, 40 parts (0 on the bottom side), 29 nets.

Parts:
C1, C4, C7, C9, C10, C12, C13, C14, C15: 100nF; 0603_C
C2, C3: 22pF; 0603_C
C5, C6: 18pF; 0603_C
C8, C11: 10uF; 0603_C
D1: 0603_红灯; 0603_LED_S1
D2: 0603_蓝灯; 0603_LED_S1
D3: 0603_绿灯; 0603_LED_S1
J1: USB_C_Receptacle_USB2.0; USB-Type-C
J2, J3: Header5; PinHeader_1x05_P2.54mm_Vertical
J4: Conn_01x05_Male; PinHeader_1x05_P2.54mm_Vertical
R1, R2: 100K; 0603_R
R3: 10K; 0603_R
R4: 100k; 0603_R
R5: 100R; 0603_R
R6, R7: 4.7K; 0603_R
R8, R9, R14: 1K; 0603_R
R10: 1.5k; 0603_R
R11, R12: 33R; 0603_R
R13: 0402_0Ω__0R0_1%; 0402_R
R15: NC/1M; 0603_R
U1: STM32F103C8Tx; LQFP-48_7x7mm_P0.5mm
U2: SPX3819M5-L; SOT23-5
Y1: 8MHz; Crystal_SMD_Abracon_ABM3C-4Pin_5.0x3.2mm

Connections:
+3V3: C9.1, C10.1, C11.1, C12.1, C13.1, C14.1, C15.1, D1.A, D3.A, J2.1, J4.1, R1.2, R4.1, R6.1, R10.1, U1.1, U1.9, U1.24, U1.36, U1.48, U2.5
+5V: C7.1, C8.1, J3.1, R13.2, U2.1, U2.3
/IF_NRESET: C1.1, J4.4, R1.1, U1.7
/IF_SWCLK: J4.3, U1.37
/IF_SWDIO: J4.2, U1.34
/LED_COM_GRN: R14.2, U1.41
/LED_DAP_BLUE: R9.2, U1.42
/LED_PWR_RED: R8.2, U1.30
/TGT_NRESET: C4.1, J2.5, R4.2, U1.18
/TGT_RX: J3.2, U1.13
/TGT_SWCLK: J2.4, U1.15, U1.26
/TGT_SWDIO: J2.2, R5.1, U1.27
/TGT_SWO: J3.4, U1.31
/TGT_TX: J3.3, U1.12
/TGT_USB_D+: C6.1, R12.2, U1.33
/TGT_USB_D-: C5.1, R11.2, U1.32
GND: C1.2, C2.2, C3.2, C4.2, C5.2, C6.2, C7.2, C8.2, C9.2, C10.2, C11.2, C12.2, C13.2, C14.2, C15.2, D2.K, J1.A1, J2.3, J3.5, J4.5, R2.1, R3.1, R7.2, U1.8, U1.20, U1.23, U1.35, U1.47, U2.2, Y1.2, Y1.4
unnamed: C2.1, R15.1, U1.5, Y1.1
unnamed: C3.1, R15.2, U1.6, Y1.3
unnamed: D1.K, R8.1
unnamed: D2.A, R9.1
unnamed: D3.K, R14.1
unnamed: J1.A6, R10.2, R12.1
unnamed: J1.A7, R11.1
unnamed: R2.2, U1.44
unnamed: R3.2, U1.2
unnamed: R5.2, U1.25
unnamed: R6.2, R7.1, U1.10
VBUS: J1.A4, R13.1

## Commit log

2020-01-01 1 WDebug_Tool 2 DAPLink 3 matrix_display
2020-01-01 修改电阻电容封装
2020-04-11 第二版可以正常烧写，有串口
2020-04-12 WDebug——DAPLinkV1.2 调整中
2020-04-13 修改好DAPLinkV1.2版本
2020-04-14 提交修改USB type-C和按键 3D模型
2020-04-14 解决框图生成模型问题
2020-04-15 添加所用封装库
2020-04-17 WDebug_KiCAD_V1.3 修改串口RX和TX相反，16pin接口定义相反
2020-04-23 修改matrix_display16_32 3D模型封装
2020-05-15 WDebug_DAPLink V1.4 1 修改 16Pin接口SWCLK和SWDIO反了。 2 3.3V不直接连接到16pin和18pin接口 3 AMS1117换成线性3819
2020-07-15 修正DAPlink 1.5版本 串口信号修改，新加一路串口
2021-02-20 提交CDC 模拟初始工程
2021-02-22 修改LED IO/修改SWO uart为3
2022-01-11 新加转接板，准备V1.7版本的修改思路和改进点
2022-01-11 添加WDebug固件工程
2022-01-11 提交历次打样的pcb和3D模型
2022-01-11 修改转接板接口定义
2022-01-12 添加typec封装和3D模型
2022-01-12 修改V1.7版本 typec元件切换/晶振封装切换/SWD接口切换/新加3.3v调试电阻
2022-01-12 更新typec符号封装
2022-01-12 一点修改和生成打样文件
2022-02-28 修改点阵铜柱洞3.5MM 修改连接接口2.54MM
2022-03-14 修改matrixDisplay1632控制版
2024-01-22 add Wspectrum
